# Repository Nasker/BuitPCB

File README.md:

# BuitPCB
Repository for the Buït's PCB Kicad Project

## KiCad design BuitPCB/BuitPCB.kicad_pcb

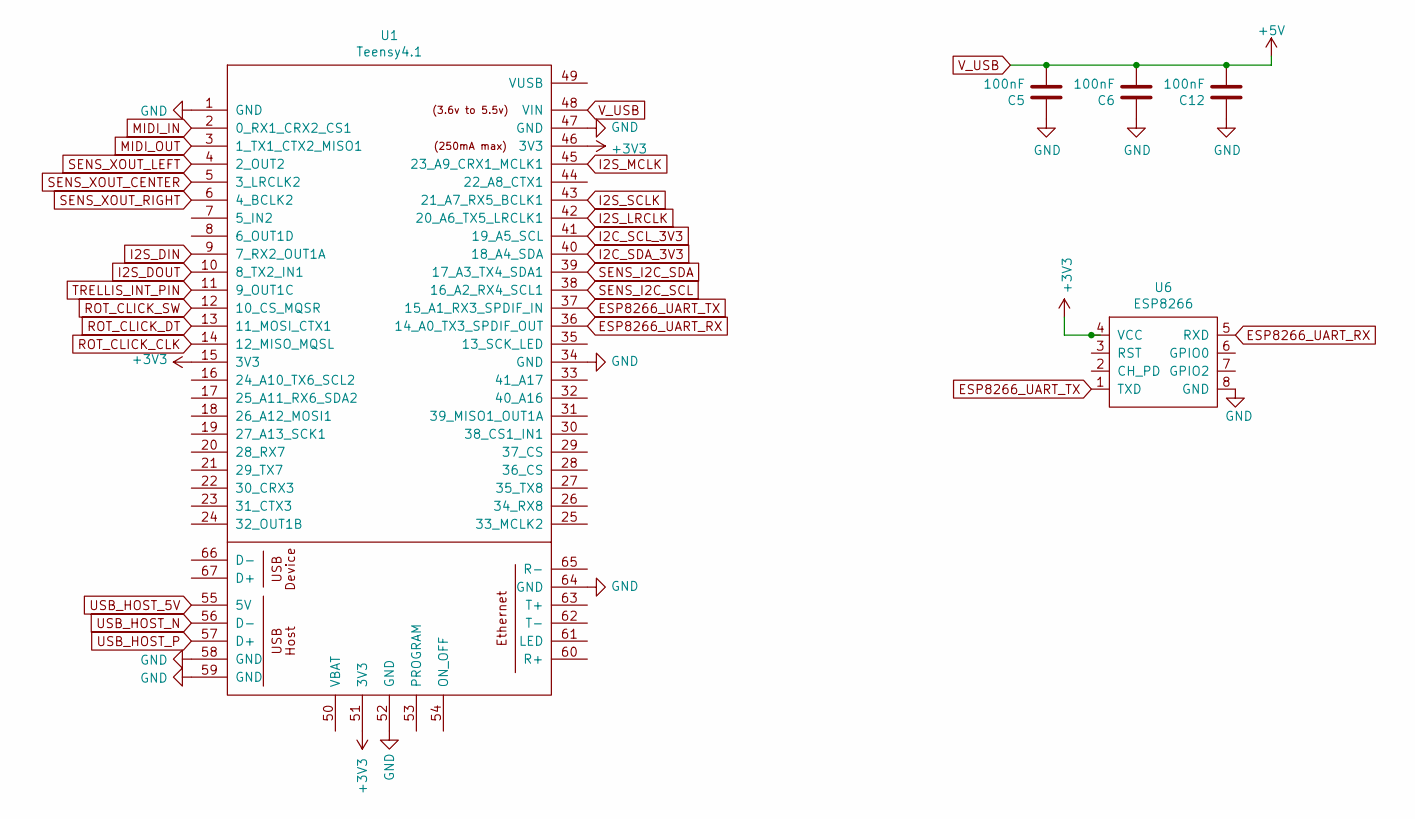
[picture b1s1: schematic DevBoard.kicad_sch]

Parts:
C5, C6, C12: 100nF; C_0805_2012Metric
U1: Teensy4.1; Teensy41
U6: ESP8266; ESP82SerialTransceiver

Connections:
+3V3: U1.15 (3V3), U1.46 (3V3), U1.51 (3V3), U6.4 (VCC); also elsewhere on the board
ESP8266_UART_RX: U1.36 (14_A0_TX3_SPDIF_OUT), U6.5 (RXD); also elsewhere on the board
ESP8266_UART_TX: U1.37 (15_A1_RX3_SPDIF_IN), U6.1 (TXD); also elsewhere on the board
GND: C5.1, C6.1, C12.1, U1.1 (GND), U1.34 (GND), U1.47 (GND), U1.52 (GND), U1.58 (GND), U1.59 (GND), U1.64 (GND), U6.8 (GND); also elsewhere on the board
V_USB: C5.2, C6.2, C12.2, U1.48 (VIN); also elsewhere on the board

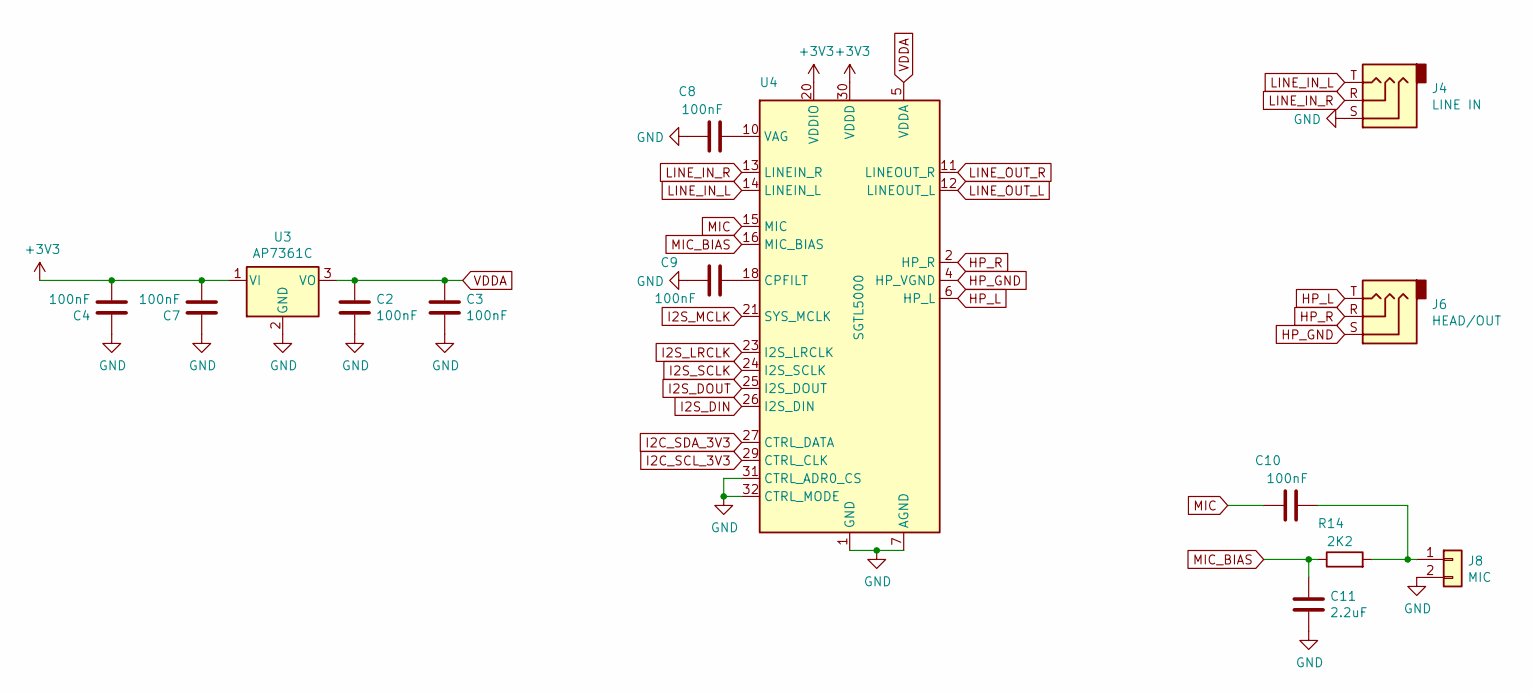
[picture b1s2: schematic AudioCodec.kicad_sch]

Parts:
C2, C3, C4, C7, C8, C9, C10: 100nF; C_0805_2012Metric
C11: 2.2uF; C_0805_2012Metric
J4: LINE IN; MJ4435
J6: HEAD/OUT; MJ4435
J8: MIC; JST_XH_B2B-XH-A_1x02_P2.50mm_Vertical
R14: 2K2; R_0805_2012Metric
U3: AP7361C; SOT-23
U4: SGTL5000; QFN-32-1EP_5x5mm_P0.5mm_EP3.6x3.6mm

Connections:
+3V3: C4.2, C7.2, U3.1 (VI), U4.20 (VDDIO), U4.30 (VDDD); also elsewhere on the board
GND: C2.2, C3.2, C4.1, C7.1, C8.1, C9.1, C11.2, J4.S, J8.2, U3.2 (GND), U4.1 (GND), U4.3 (GND), U4.7 (AGND), U4.31 (CTRL_ADR0_CS), U4.32 (CTRL_MODE), U4.33 (GND); also elsewhere on the board
HP_GND: J6.S, U4.4 (HP_VGND)
HP_L: J6.T, U4.6 (HP_L)
HP_R: J6.R, U4.2 (HP_R)
I2C_SCL_3V3: U4.29 (CTRL_CLK); also elsewhere on the board
I2C_SDA_3V3: U4.27 (CTRL_DATA); also elsewhere on the board
I2S_DIN: U4.26 (I2S_DIN); also elsewhere on the board
I2S_DOUT: U4.25 (I2S_DOUT); also elsewhere on the board
I2S_LRCLK: U4.23 (I2S_LRCLK); also elsewhere on the board
I2S_MCLK: U4.21 (SYS_MCLK); also elsewhere on the board
I2S_SCLK: U4.24 (I2S_SCLK); also elsewhere on the board
LINE_IN_L: J4.T, U4.14 (LINEIN_L)
LINE_IN_R: J4.R, U4.13 (LINEIN_R)
LINE_OUT_L: U4.12 (LINEOUT_L)
LINE_OUT_R: U4.11 (LINEOUT_R)
MIC: C10.1, U4.15 (MIC)
MIC_BIAS: C11.1, R14.1, U4.16 (MIC_BIAS)
unnamed: C8.2, U4.10 (VAG)
unnamed: C9.2, U4.18 (CPFILT)
unnamed: C10.2, J8.1, R14.2
VDDA: C2.1, C3.1, U3.3 (VO), U4.5 (VDDA)

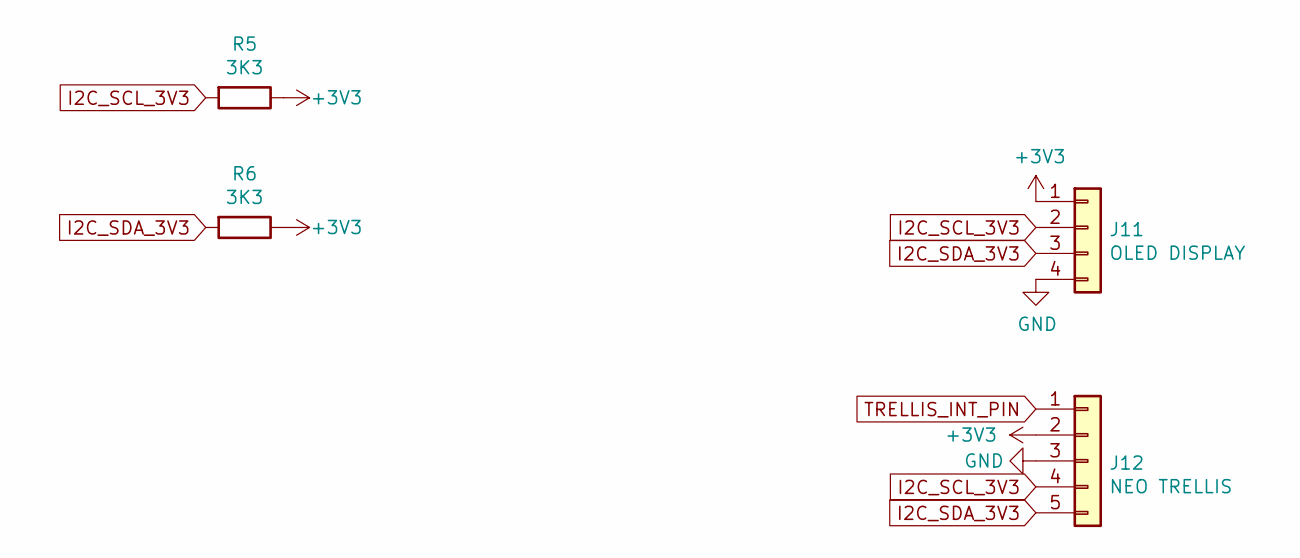
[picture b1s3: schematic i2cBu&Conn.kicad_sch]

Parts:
J11: OLED DISPLAY; JST_XH_B4B-XH-A_1x04_P2.50mm_Vertical
J12: NEO TRELLIS; JST_XH_B5B-XH-A_1x05_P2.50mm_Vertical
R5, R6: 3K3; R_0805_2012Metric

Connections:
+3V3: J11.1, J12.2, R5.1, R6.1; also elsewhere on the board
GND: J11.4, J12.3; also elsewhere on the board
I2C_SCL_3V3: J11.2, J12.4, R5.2; also elsewhere on the board
I2C_SDA_3V3: J11.3, J12.5, R6.2; also elsewhere on the board
TRELLIS_INT_PIN: J12.1; also elsewhere on the board

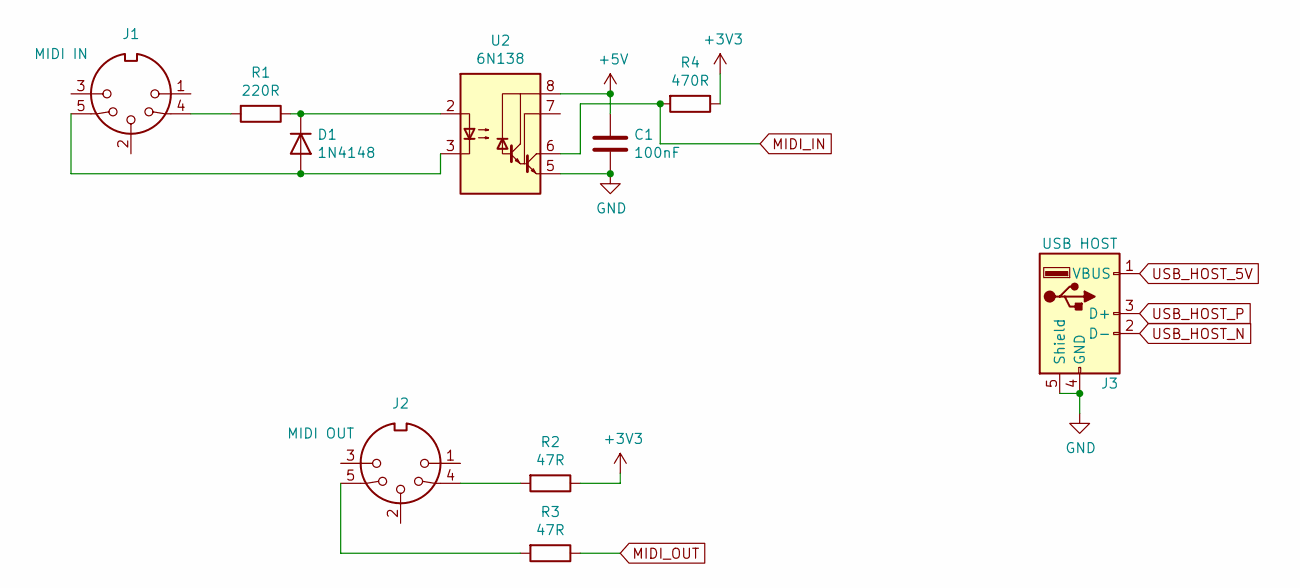
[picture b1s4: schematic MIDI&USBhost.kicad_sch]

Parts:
C1: 100nF; C_0805_2012Metric
D1: 1N4148; D_0805_2012Metric
J1: MIDI IN; DJ005
J2: MIDI OUT; DJ005
J3: USB HOST; USB_A_Stewart_SS-52100-001_Horizontal
R1: 220R; R_0805_2012Metric
R2, R3: 47R; R_0805_2012Metric
R4: 470R; R_0805_2012Metric
U2: 6N138; DIP-8_W8.89mm_SMDSocket_LongPads

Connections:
+3V3: R2.1, R4.1; also elsewhere on the board
GND: C1.2, J3.4 (GND), J3.5 (Shield), U2.5 (GND); also elsewhere on the board
MIDI_IN: R4.2, U2.6 (VO2); also elsewhere on the board
MIDI_OUT: R3.1; also elsewhere on the board
unnamed: D1.1 (K), R1.1, U2.2 (C1)
unnamed: D1.2 (A), J1.5, U2.3 (C2)
unnamed: J1.4, R1.2
unnamed: J2.4, R2.2
unnamed: J2.5, R3.2
USB_HOST_5V: J3.1 (VBUS); also elsewhere on the board
USB_HOST_N: J3.2 (D-); also elsewhere on the board
USB_HOST_P: J3.3 (D+); also elsewhere on the board
V_USB: C1.1, U2.8 (VCC); also elsewhere on the board

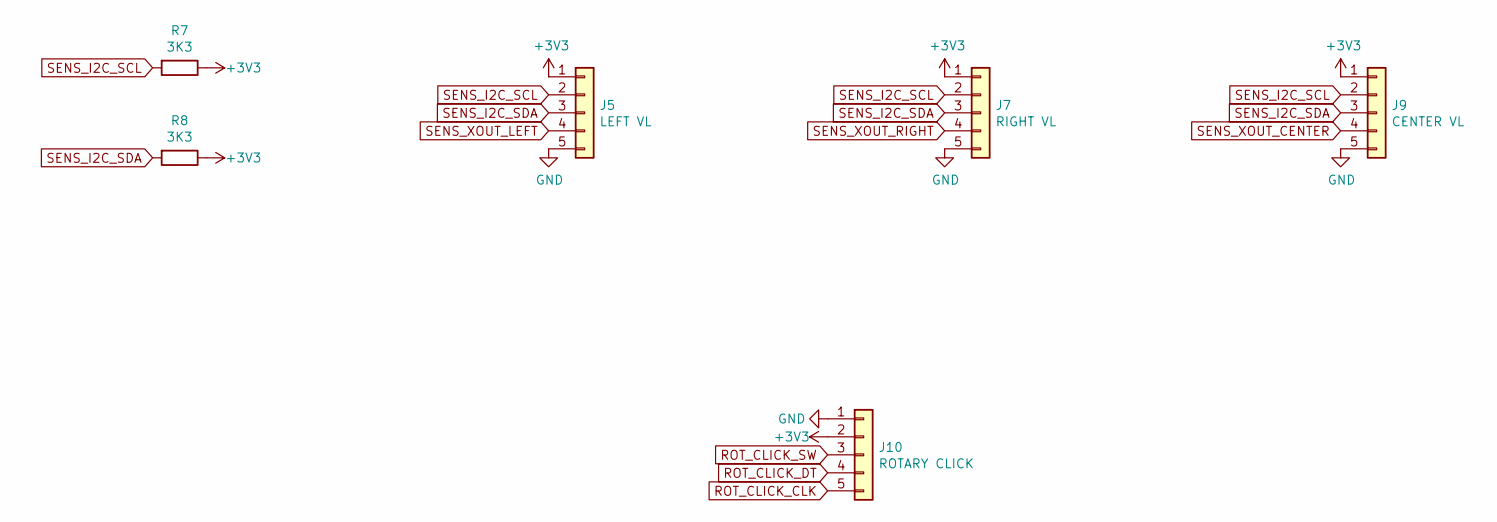
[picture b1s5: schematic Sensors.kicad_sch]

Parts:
J5: LEFT VL; JST_XH_B5B-XH-A_1x05_P2.50mm_Vertical
J7: RIGHT VL; JST_XH_B5B-XH-A_1x05_P2.50mm_Vertical
J9: CENTER VL; JST_XH_B5B-XH-A_1x05_P2.50mm_Vertical
J10: ROTARY CLICK; JST_XH_B5B-XH-A_1x05_P2.50mm_Vertical
R7, R8: 3K3; R_0805_2012Metric

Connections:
+3V3: J5.1, J7.1, J9.1, J10.2, R7.1, R8.1; also elsewhere on the board
GND: J5.5, J7.5, J9.5, J10.1; also elsewhere on the board
ROT_CLICK_CLK: J10.5; also elsewhere on the board
ROT_CLICK_DT: J10.4; also elsewhere on the board
ROT_CLICK_SW: J10.3; also elsewhere on the board
SENS_I2C_SCL: J5.2, J7.2, J9.2, R7.2; also elsewhere on the board
SENS_I2C_SDA: J5.3, J7.3, J9.3, R8.2; also elsewhere on the board
SENS_XOUT_CENTER: J9.4; also elsewhere on the board
SENS_XOUT_LEFT: J5.4; also elsewhere on the board
SENS_XOUT_RIGHT: J7.4; also elsewhere on the board

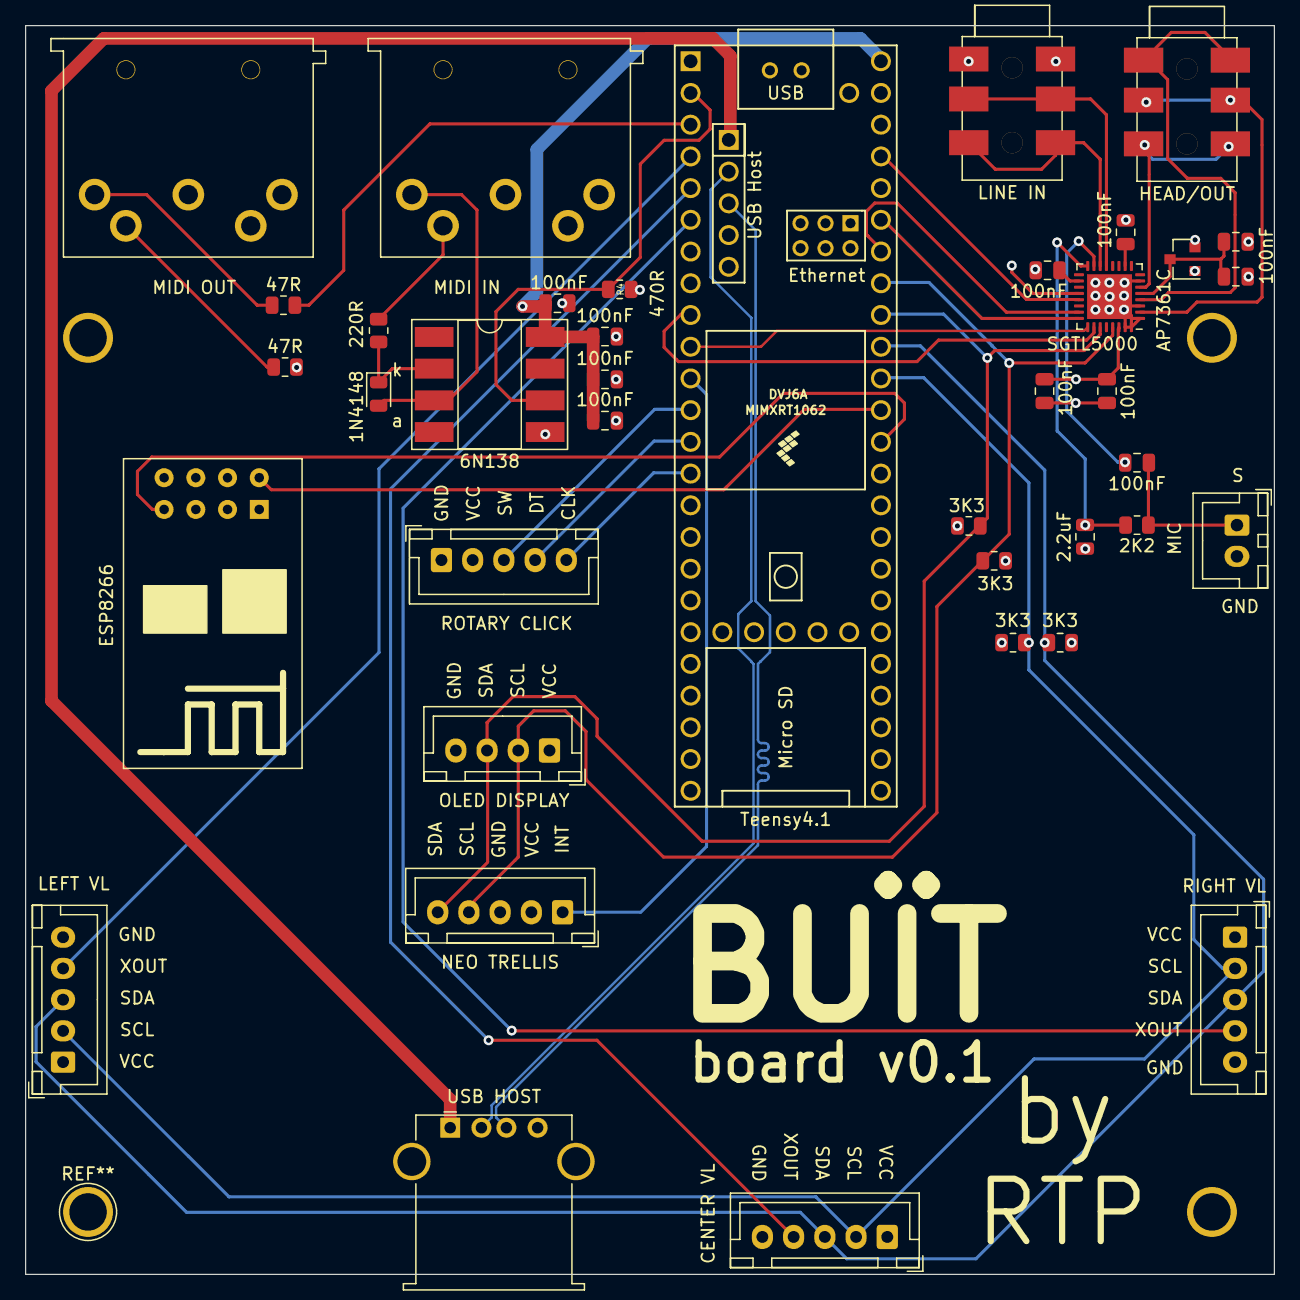
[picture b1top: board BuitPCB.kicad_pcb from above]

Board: 4 copper layers, 100.0 x 100.0 mm, 39 parts (0 on the bottom side), 42 nets.

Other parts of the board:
1º: Teensy4.1; Teensy41

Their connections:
+3V3: 1º.15 (3V3), 1º.46 (3V3), 1º.51 (3V3); also elsewhere on the board
ESP8266_UART_RX: 1º.36 (14_A0_TX3_SPDIF_OUT); also elsewhere on the board
ESP8266_UART_TX: 1º.37 (15_A1_RX3_SPDIF_IN); also elsewhere on the board
GND: 1º.1 (GND), 1º.34 (GND), 1º.47 (GND), 1º.52 (GND), 1º.58 (GND), 1º.59 (GND), 1º.64 (GND); also elsewhere on the board
I2C_SCL_3V3: 1º.41 (19_A5_SCL); also elsewhere on the board
I2C_SDA_3V3: 1º.40 (18_A4_SDA); also elsewhere on the board
I2S_DIN: 1º.9 (7_RX2_OUT1A); also elsewhere on the board
I2S_DOUT: 1º.10 (8_TX2_IN1); also elsewhere on the board
I2S_LRCLK: 1º.42 (20_A6_TX5_LRCLK1); also elsewhere on the board
I2S_MCLK: 1º.45 (23_A9_CRX1_MCLK1); also elsewhere on the board
I2S_SCLK: 1º.43 (21_A7_RX5_BCLK1); also elsewhere on the board
MIDI_IN: 1º.2 (0_RX1_CRX2_CS1); also elsewhere on the board
MIDI_OUT: 1º.3 (1_TX1_CTX2_MISO1); also elsewhere on the board
ROT_CLICK_CLK: 1º.14 (12_MISO_MQSL); also elsewhere on the board
ROT_CLICK_DT: 1º.13 (11_MOSI_CTX1); also elsewhere on the board
ROT_CLICK_SW: 1º.12 (10_CS_MQSR); also elsewhere on the board
SENS_I2C_SCL: 1º.38 (16_A2_RX4_SCL1); also elsewhere on the board
SENS_I2C_SDA: 1º.39 (17_A3_TX4_SDA1); also elsewhere on the board
SENS_XOUT_CENTER: 1º.5 (3_LRCLK2); also elsewhere on the board
SENS_XOUT_LEFT: 1º.4 (2_OUT2); also elsewhere on the board
SENS_XOUT_RIGHT: 1º.6 (4_BCLK2); also elsewhere on the board
TRELLIS_INT_PIN: 1º.11 (9_OUT1C); also elsewhere on the board
USB_HOST_5V: 1º.55 (5V); also elsewhere on the board
USB_HOST_N: 1º.56 (D-); also elsewhere on the board
USB_HOST_P: 1º.57 (D+); also elsewhere on the board
V_USB: 1º.48 (VIN); also elsewhere on the board

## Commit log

2021-12-02 First commit with design files, main components placed
2021-12-03 Added sheets and connectors
2021-12-03 Added most of components, few pending
2021-12-09 Added sensors connectors
2021-12-16 Updated adding battery management sheet and componnents to PCB
2021-12-17 Updated adding esp8266 transceiver module
2022-01-19 Updated to almost every component and started routing
2022-02-09 Added drills on pcb
2022-04-20 Updated almost to final 0.1 version
2022-04-21 updated with 3dmodels
2022-04-21 updated with almost al 3d models and esp001 rotated
2022-04-22 Updated and send to fab
2022-04-23 Updated Teensy4 3d model
